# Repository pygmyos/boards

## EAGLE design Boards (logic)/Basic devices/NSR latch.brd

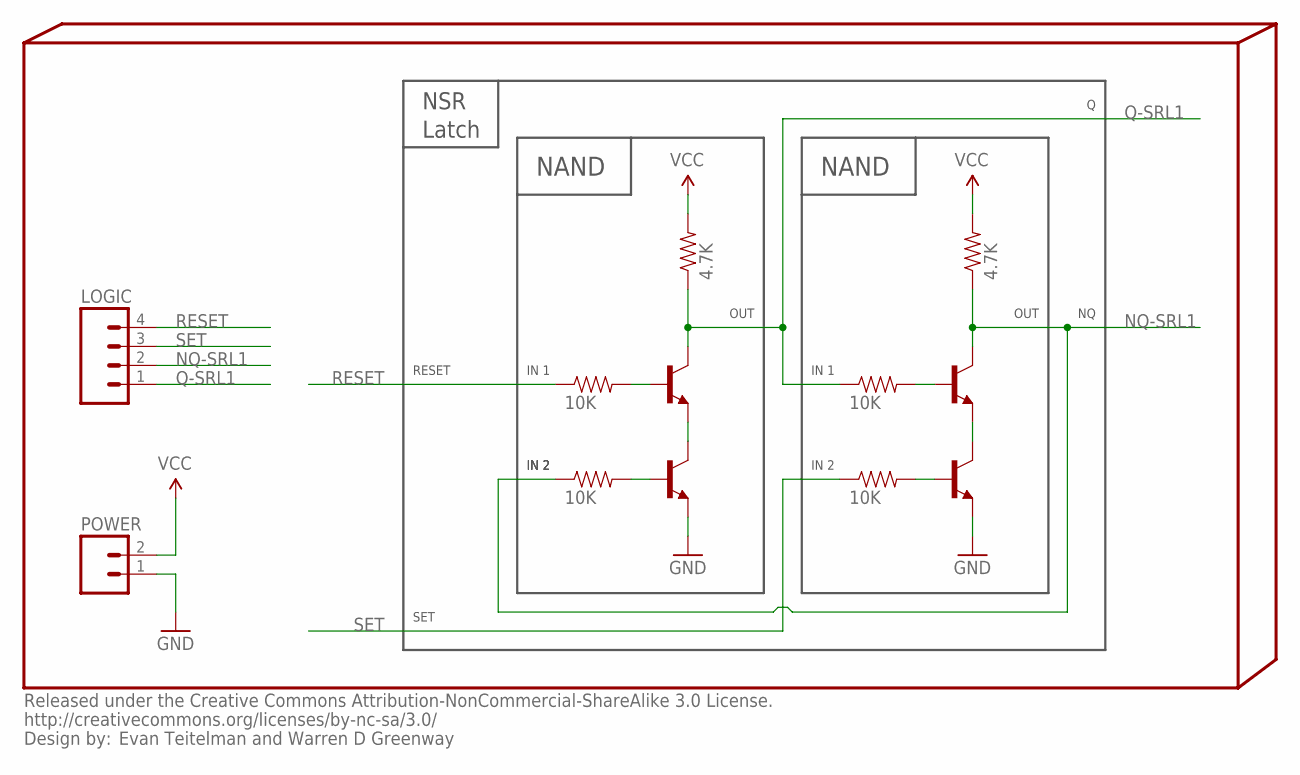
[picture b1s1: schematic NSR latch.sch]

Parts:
INFO4: Evan Teitelman and Warren D Greenway; %CC-NC-SA
LOGIC: M04PTH; 1X04
POWER: M02PTH; 1X02
PUR-NAND1, PUR-NAND2: 4.7K; 0402-RES
Q1-NAND1, Q1-NAND2, Q2-NAND1, Q2-NAND2: TRANSISTOR_NPNSOT23; SOT23
R1-NAND1, R1-NAND2, R2-NAND1, R2-NAND2: 10K; 0402-RES

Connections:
GND: POWER.1, Q2-NAND1.2 (E), Q2-NAND2.2 (E)
unnamed: Q1-NAND2.1 (B), R1-NAND2.2
unnamed: Q2-NAND2.1 (B), R2-NAND1.2
unnamed: Q1-NAND1.1 (B), R1-NAND1.2
unnamed: Q2-NAND1.1 (B), R2-NAND2.2
NQ-SRL1: LOGIC.2, PUR-NAND1.1, Q1-NAND1.3 (C), R2-NAND1.1
Q-Q-NAND1: Q1-NAND1.2 (E), Q2-NAND1.3 (C)
Q-Q-NAND2: Q1-NAND2.2 (E), Q2-NAND2.3 (C)
Q-SRL1: LOGIC.1, PUR-NAND2.1, Q1-NAND2.3 (C), R1-NAND1.1
RESET: LOGIC.4, R1-NAND2.1
SET: LOGIC.3, R2-NAND2.1
VCC: POWER.2, PUR-NAND1.2, PUR-NAND2.2

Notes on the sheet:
IN 2
NSR
SET
RESET
Latch
NAND
OUT
IN 1

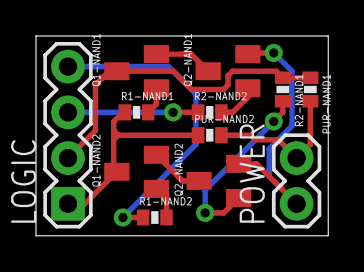
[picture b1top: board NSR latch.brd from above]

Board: 2 copper layers, 16.2 x 11.1 mm, 13 parts (0 on the bottom side), 12 nets.
